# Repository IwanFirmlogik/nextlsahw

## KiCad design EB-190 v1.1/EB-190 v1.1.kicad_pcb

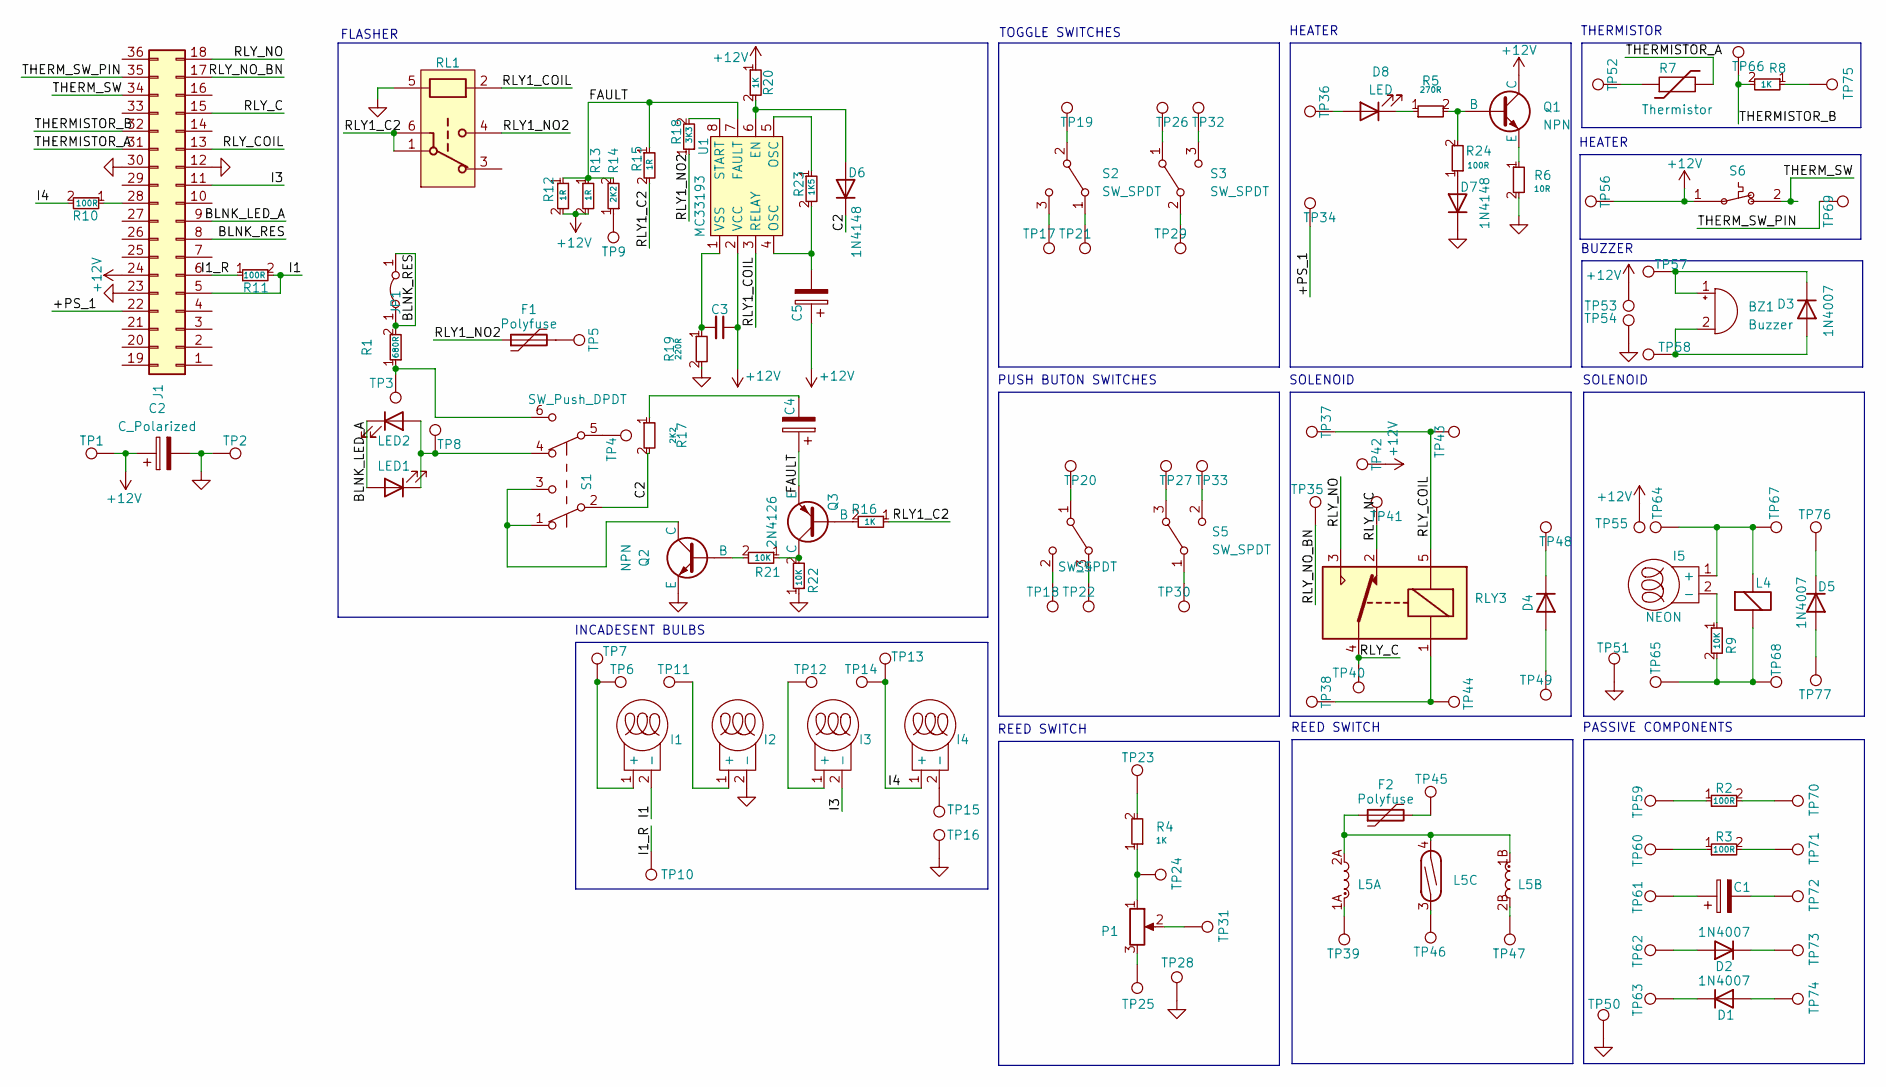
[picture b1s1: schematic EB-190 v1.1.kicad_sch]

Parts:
BZ1: Buzzer; BUZZER 12mm Pitch 7.6mm
C1: C_Polarized; CP_Radial_D10.0mm_P5.00mm
C2: C_Polarized; CP_Radial_D6.3mm_P2.50mm
C3: 100nF; C_0603_1608Metric
C4, C5: C_Polarized; CP_Radial_D5.0mm_P2.50mm
D1, D2, D3, D4, D5: 1N4007; D_DO-41_SOD81_P10.16mm_Horizontal
D6, D7: 1N4148; D_DO-35_SOD27_P7.62mm_Horizontal
D8: LED; LED_D3.0mm
F1, F2: Polyfuse; C_Disc_D4.3mm_W1.9mm_P5.00mm
I1, I2, I3, I4: INCADESCENT-BULB; INCADESCENT BULB
I5: NEON; NEON BULB
J1: Conn_02x18_Top_Bottom; Centronics Connector
JP1: Jumper_2_Bridged; TestPoint_Bridge_Pitch3.81mm_Drill1.3mm
L4: ElectromagneticActor; ADAFruit Solenoid
L5: Dual Coil with Reed Relay
LED1, LED2: LED; LED_D3.0mm
P1: R_Potentiometer; TRIM_3310Y-011-102L
Q1: NPN; TO-220F-3_Horizontal_TabDown
Q2: NPN; TO-92
Q3: 2N4126; TO-92
R1: 680R; R_Axial_DIN0207_L6.3mm_D2.5mm_P10.16mm_Horizontal
R2, R3: 100R; R_Axial_DIN0614_L14.3mm_D5.7mm_P25.40mm_Horizontal
R4, R8, R16, R20: 1K; R_Axial_DIN0207_L6.3mm_D2.5mm_P10.16mm_Horizontal
R5: 270R; R_Axial_DIN0207_L6.3mm_D2.5mm_P10.16mm_Horizontal
R6: 10R; R_Axial_DIN0516_L15.5mm_D5.0mm_P20.32mm_Horizontal
R7: Thermistor; R_Radial_Power_L11.0mm_W7.0mm_P5.00mm
R9, R21, R22: 10K; R_Axial_DIN0207_L6.3mm_D2.5mm_P10.16mm_Horizontal
R10, R11: 100R; R_0603_1608Metric
R12, R13, R15: 1R; R_Axial_DIN0309_L9.0mm_D3.2mm_P12.70mm_Horizontal
R14, R17: 2K2; R_Axial_DIN0207_L6.3mm_D2.5mm_P10.16mm_Horizontal
R18: 3K3; R_Axial_DIN0207_L6.3mm_D2.5mm_P10.16mm_Horizontal
R19: 220R; R_Axial_DIN0207_L6.3mm_D2.5mm_P10.16mm_Horizontal
R23: 1K5; R_Axial_DIN0207_L6.3mm_D2.5mm_P10.16mm_Horizontal
R24: 100R; R_Axial_DIN0207_L6.3mm_D2.5mm_P10.16mm_Horizontal
RL1: JRC-23F
RLY3: DIPxx-1Cxx-51x; RELAY_G2R-1 AC12_OMR
S1: SW_Push_DPDT; DPDT MECHANICAL
S2, S3, S4, S5: SW_SPDT; BUTTON-SPDT-MECHANICAL
S6: C_Disc_D4.3mm_W1.9mm_P5.00mm
TP1, TP2, TP3, TP4, TP5, TP6, TP7, TP8, TP9, TP10, TP11, TP12, TP13, TP14, TP15, TP16, TP17, TP18, TP19, TP20, TP21, TP22, TP23, TP24, TP25, TP26, TP27, TP28, TP29, TP30, TP31, TP32, TP33, TP34, TP35, TP36, TP37, TP38, TP39, TP40, TP41, TP42, TP43, TP44, TP45, TP46, TP47, TP48, TP49, TP50, TP51, TP52, TP53, TP54, TP55, TP56, TP57, TP58, TP59, TP60, TP61, TP62, TP63, TP64, TP65, TP66, TP67, TP68, TP69, TP70, TP71, TP72, TP73, TP74, TP75, TP76, TP77: TestPoint; 2mm BANANNA PLUG
U1: MC33193; DIP-8_W7.62mm

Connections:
+12V: C2.1, C3.1, C5.1, J1.24, Q1.2 (C), R12.2, R13.2, R20.1, S6.1, TP1.1, TP42.1, TP53.1, TP55.1, TP56.1, U1.2 (VCC)
/+PS_1: J1.22, TP34.1
/BLNK_LED_A: J1.9, LED1.2 (A), LED2.1 (K)
/BLNK_RES: J1.8, JP1.1 (A), R1.2
/C2: D6.1 (K), R17.2, S1.2 (B)
/FAULT: C4.1, Q3.1 (E), R12.1, R13.1, R14.2, R15.1, U1.7 (FAULT)
/I1: I1.2 (-), J1.5, R11.2
/I1_R: J1.6, R11.1, TP10.1
/I3: I3.2 (-), J1.11
/I4: I4.1 (+), R10.2, TP13.1, TP14.1
/RLY1_C2: R15.2, R16.1, RL1.1, RL1.6
/RLY1_COIL: RL1.2, U1.3 (RELAY)
/RLY1_NO2: F1.1, R18.1, RL1.4
/RLY_C: J1.15, RLY3.4, TP40.1
/RLY_COIL: J1.13, RLY3.5, TP37.1, TP43.1
/RLY_NC: RLY3.2, TP41.1
/RLY_NO: J1.18, RLY3.3
/RLY_NO_BN: J1.17, TP35.1
/THERMISTOR_A: J1.31, R7.2
/THERMISTOR_B: J1.32, R8.2, TP66.1
/THERM_SW: J1.34, S6.2
/THERM_SW_PIN: J1.35, TP69.1
GND: C2.2, D7.1 (K), I2.2 (-), J1.12, J1.23, J1.30, Q2.1 (E), R6.2, R19.2, R22.1, RL1.5, TP2.1, TP16.1, TP28.1, TP50.1, TP51.1, TP54.1
unnamed: BZ1.2 (+), D3.2 (A), TP58.1
unnamed: BZ1.1 (-), D3.1 (K), TP57.1
unnamed: C1.1, TP61.1
unnamed: C1.2, TP72.1
unnamed: C4.2, R17.1
unnamed: C5.2, R23.2, U1.4 (OSC)
unnamed: D1.2 (A), TP74.1
unnamed: D1.1 (K), TP63.1
unnamed: D2.2 (A), TP62.1
unnamed: D2.1 (K), TP73.1
unnamed: D4.2 (A), TP49.1
unnamed: D4.1 (K), TP48.1
unnamed: D5.2 (A), TP77.1
unnamed: D5.1 (K), TP76.1
unnamed: D6.2 (A), R20.2, U1.6 (EN)
unnamed: D7.2 (A), R24.1
unnamed: D8.2 (A), TP36.1
unnamed: D8.1 (K), R5.1
unnamed: F1.2, TP5.1
unnamed: F2.1, L5.1B, L5.2A, L5.4
unnamed: F2.2, TP45.1
unnamed: I1.1 (+), TP6.1, TP7.1
unnamed: I2.1 (+), TP11.1
unnamed: I3.1 (+), TP12.1
unnamed: I4.2 (-), TP15.1
unnamed: I5.1 (+), L4.1 (-), TP64.1, TP67.1
unnamed: I5.2 (-), R9.1
unnamed: J1.28, R10.1
unnamed: L4.2 (+), R9.2, TP65.1, TP68.1
unnamed: L5.1A, TP39.1
unnamed: L5.2B, TP47.1
unnamed: L5.3, TP46.1
unnamed: LED1.1 (K), LED2.2 (A), S1.4 (A), TP8.1
unnamed: P1.1, R4.1, TP24.1
unnamed: P1.2, TP31.1
unnamed: P1.3, TP25.1
unnamed: Q1.1 (B), R5.2, R24.2
unnamed: Q1.3 (E), R6.1
unnamed: Q2.2 (B), R21.2
unnamed: Q2.3 (C), S1.1 (A), S1.3 (C)
unnamed: Q3.2 (B), R16.2
unnamed: Q3.3 (C), R21.1, R22.2
unnamed: R1.1, S1.6 (C), TP3.1
unnamed: R2.1, TP59.1
unnamed: R2.2, TP70.1
unnamed: R3.1, TP60.1
unnamed: R3.2, TP71.1
unnamed: R4.2, TP23.1
unnamed: R7.1, TP52.1
unnamed: R8.1, TP75.1
unnamed: R14.1, TP9.1
unnamed: R23.1, U1.5 (OSC)
unnamed: RLY3.1, TP38.1, TP44.1
unnamed: S1.5 (B), TP4.1
unnamed: S2.1 (A), TP21.1
unnamed: S2.2 (B), TP19.1
unnamed: S2.3 (C), TP17.1
unnamed: S3.1 (A), TP26.1
unnamed: S3.2 (B), TP29.1
unnamed: S3.3 (C), TP32.1
unnamed: S4.3 (A), TP22.1
unnamed: S4.1 (B), TP20.1
unnamed: S4.2 (C), TP18.1
unnamed: S5.3 (A), TP27.1
unnamed: S5.1 (B), TP30.1
unnamed: S5.2 (C), TP33.1
unnamed: R18.2, U1.8 (START)
unnamed: C3.2, R19.1, U1.1 (VSS)

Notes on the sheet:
REED SWITCH
TOGGLE SWITCHES
SOLENOID
HEATER
PASSIVE COMPONENTS
PUSH BUTON SWITCHES
FLASHER
BUZZER
INCADESENT BULBS
THERMISTOR

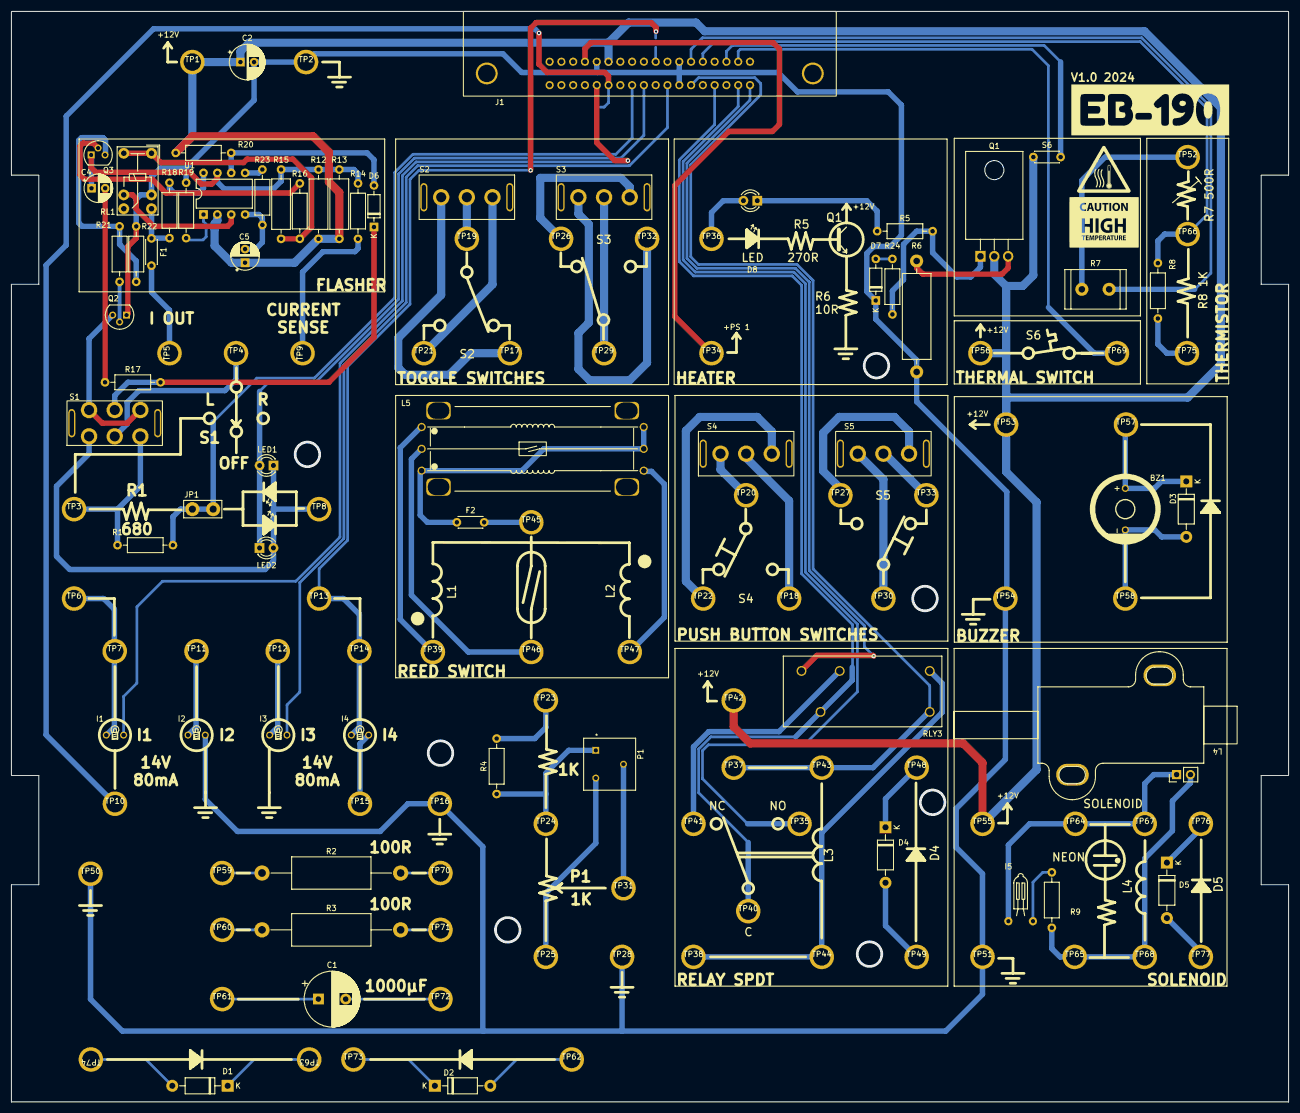
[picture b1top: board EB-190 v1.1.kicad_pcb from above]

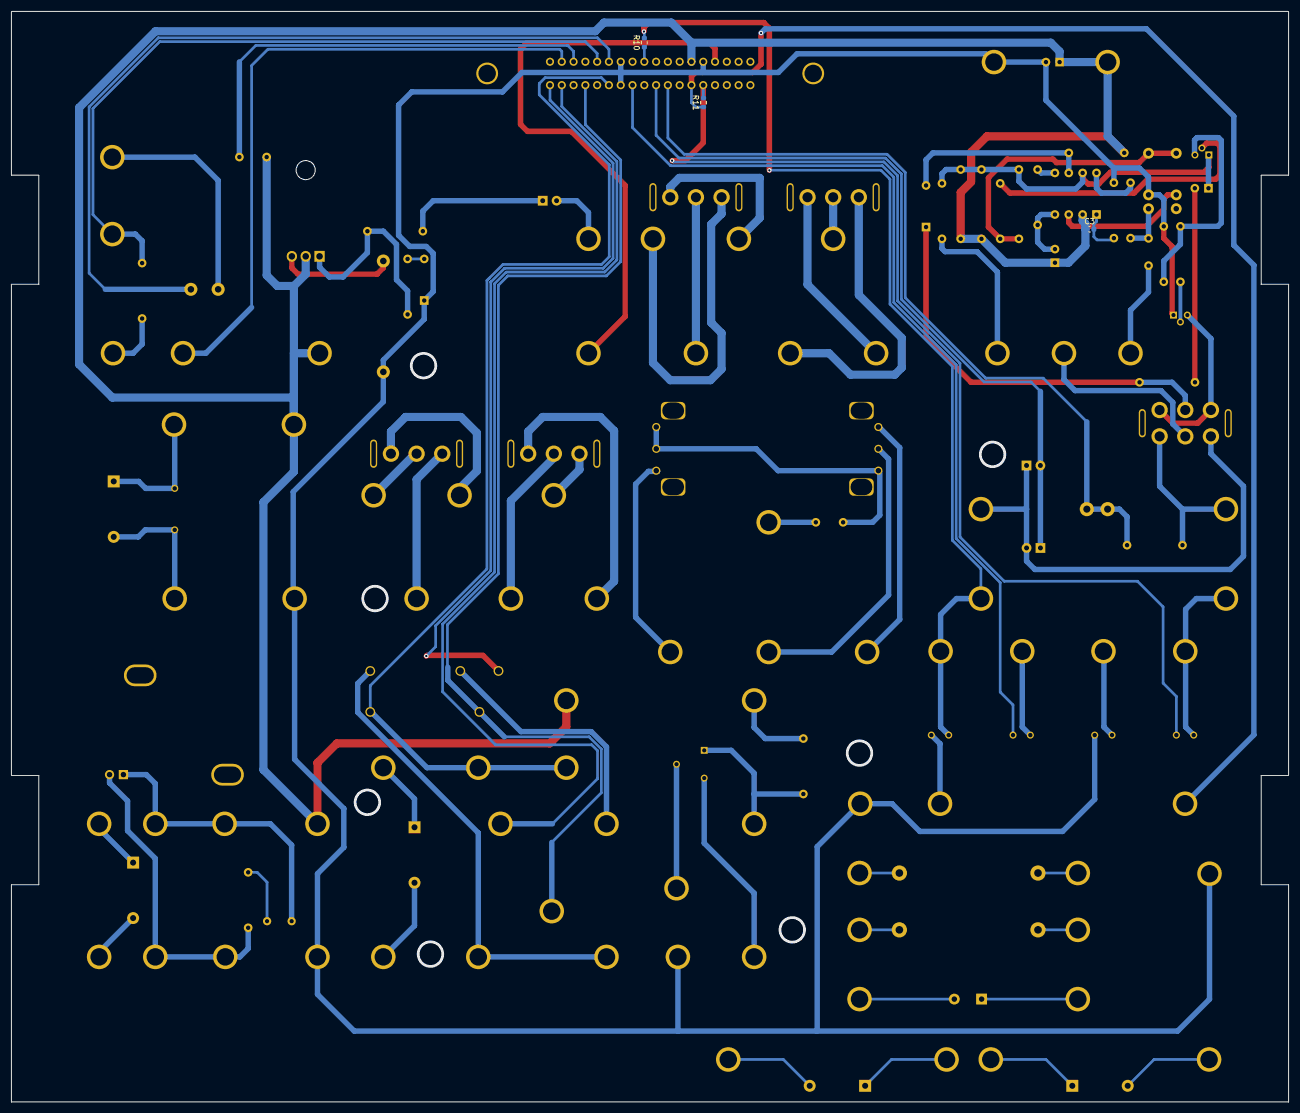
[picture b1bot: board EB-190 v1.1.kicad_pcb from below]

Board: 2 copper layers, 234.0 x 199.8 mm, 142 parts (3 on the bottom side), 91 nets.

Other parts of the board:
kibuzzard-65B90473: G***; kibuzzard-65B90473

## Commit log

2024-01-29 Initial commit - Next Level Learning
2024-01-30 EB190 - Finished - Waiting for review
2024-02-02 Fixed a small thing I noticed when the switch was desoldered.
2024-05-03 Updated some mistakes
